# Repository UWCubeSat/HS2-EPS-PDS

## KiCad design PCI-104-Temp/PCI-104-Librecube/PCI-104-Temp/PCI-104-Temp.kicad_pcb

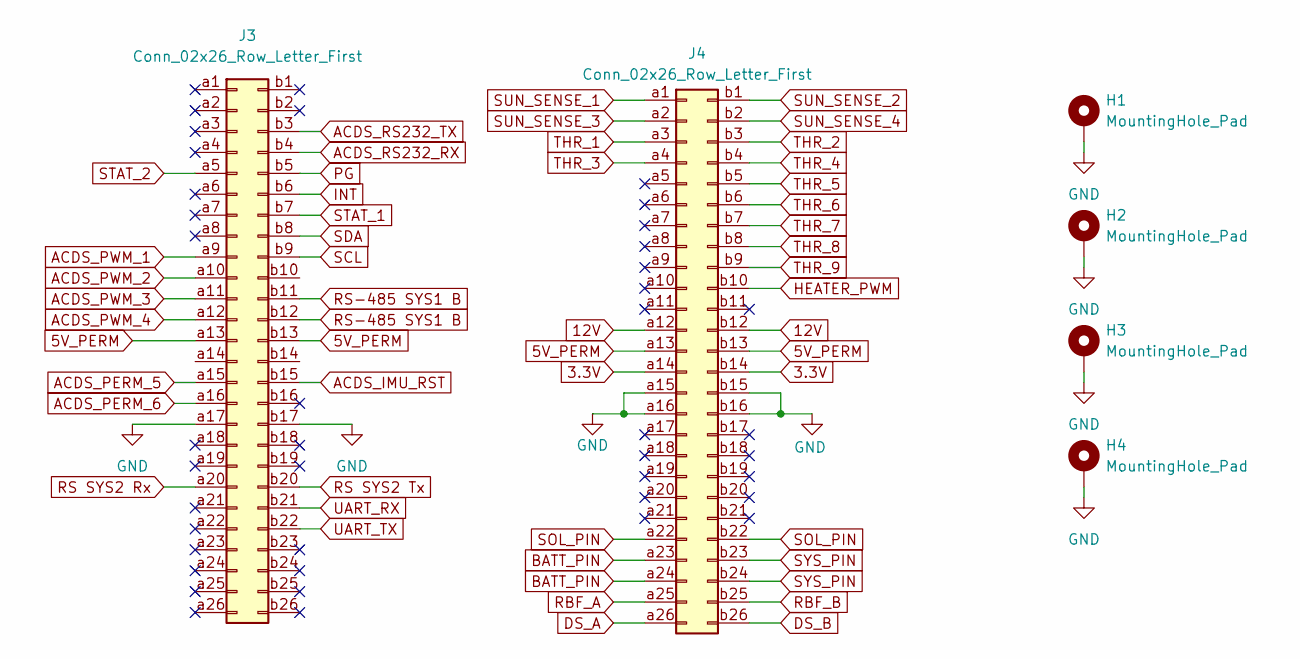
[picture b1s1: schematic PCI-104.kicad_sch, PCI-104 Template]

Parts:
H1, H2, H3, H4: MountingHole_Pad; MountingHole_3.2mm_M3_Pad
J3, J4: Conn_02x26_Row_Letter_First; PinSocket_2x26_P2.54mm_Vertical

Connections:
3.3V: J4.a14, J4.b14
5V_PERM: J3.a13, J3.b13, J4.a13, J4.b13
12V: J4.a12, J4.b12
ACDS_IMU_RST: J3.b15
ACDS_PERM_5: J3.a15
ACDS_PERM_6: J3.a16
ACDS_PWM_1: J3.a9
ACDS_PWM_2: J3.a10
ACDS_PWM_3: J3.a11
ACDS_PWM_4: J3.a12
ACDS_RS232_RX: J3.b4
ACDS_RS232_TX: J3.b3
BATT_PIN: J4.a23, J4.a24
DS_A: J4.a26
DS_B: J4.b26
GND: H1.1 (1_1), H2.1 (1_1), H3.1 (1_1), H4.1 (1_1), J3.a17, J3.b17, J4.a15, J4.a16, J4.b15, J4.b16
HEATER_PWM: J4.b10
INT: J3.b6
PG: J3.b5
RBF_A: J4.a25
RBF_B: J4.b25
RS SYS2 Rx: J3.a20
RS SYS2 Tx: J3.b20
RS-485 SYS1 B: J3.b11, J3.b12
SCL: J3.b9
SDA: J3.b8
SOL_PIN: J4.a22, J4.b22
STAT_1: J3.b7
STAT_2: J3.a5
SUN_SENSE_1: J4.a1
SUN_SENSE_2: J4.b1
SUN_SENSE_3: J4.a2
SUN_SENSE_4: J4.b2
SYS_PIN: J4.b23, J4.b24
THR_1: J4.a3
THR_2: J4.b3
THR_3: J4.a4
THR_4: J4.b4
THR_5: J4.b5
THR_6: J4.b6
THR_7: J4.b7
THR_8: J4.b8
THR_9: J4.b9
UART_RX: J3.b21
UART_TX: J3.b22

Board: 2 copper layers, 6 parts (0 on the bottom side), 8 nets, no tracks yet.

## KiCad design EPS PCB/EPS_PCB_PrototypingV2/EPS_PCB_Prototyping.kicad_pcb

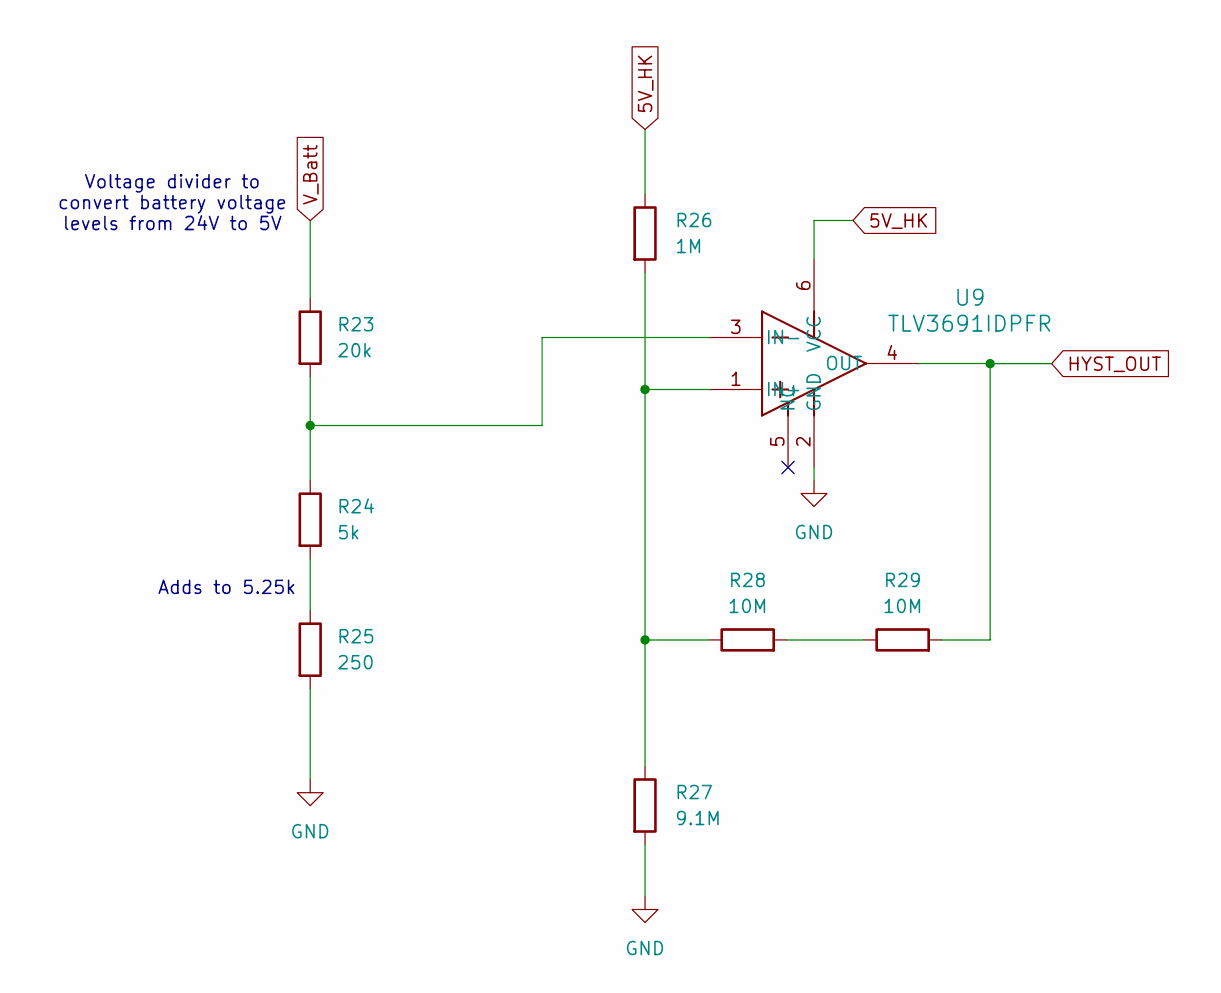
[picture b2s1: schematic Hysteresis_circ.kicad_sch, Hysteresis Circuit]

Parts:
R23: 20k; R_0603_1608Metric
R24: 5k; R_0603_1608Metric
R25: 250; R_0603_1608Metric
R26: 1M; R_1206_3216Metric
R27: 9.1M; R_1206_3216Metric
R28, R29: 10M; R_1206_3216Metric
U9: TLV3691IDPFR

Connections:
5V_HK: R26.1, U9.6 (VCC); also elsewhere on the board
GND: R25.2, R27.2, U9.2 (GND); also elsewhere on the board
HYST_OUT: R29.2, U9.4 (OUT)
unnamed: R24.2, R25.1
unnamed: R28.2, R29.1
unnamed: R26.2, R27.1, R28.1, U9.1 (IN+)
unnamed: R23.2, R24.1, U9.3 (IN-)

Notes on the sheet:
Adds to 5.25k
Voltage divider to convert battery voltage levels from 24V to 5V

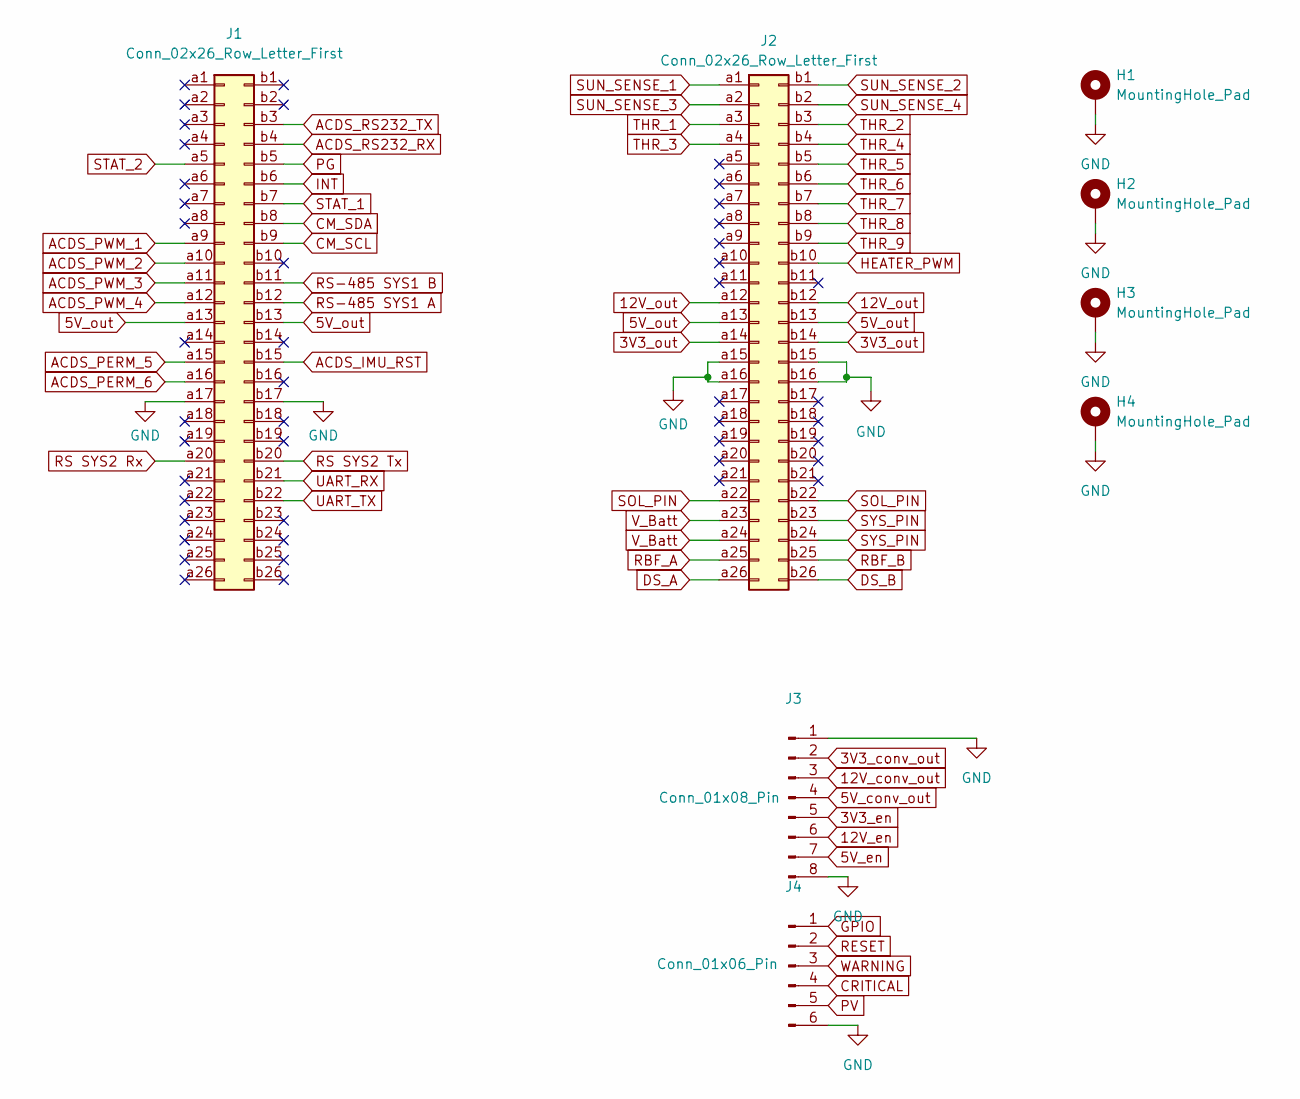
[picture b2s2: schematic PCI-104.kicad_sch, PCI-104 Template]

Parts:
H1, H2, H3, H4: MountingHole_Pad; MountingHole_3.2mm_M3_Pad
J1, J2: Conn_02x26_Row_Letter_First; PinSocket_2x26_P2.54mm_Vertical
J3: Conn_01x08_Pin; PinHeader_1x08_P2.54mm_Vertical
J4: Conn_01x06_Pin; PinHeader_1x06_P2.54mm_Horizontal

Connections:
3V3_conv_out: J3.2; also elsewhere on the board
3V3_en: J3.5; also elsewhere on the board
3V3_out: J2.a14, J2.b14; also elsewhere on the board
5V_conv_out: J3.4; also elsewhere on the board
5V_en: J3.7; also elsewhere on the board
5V_out: J1.a13, J1.b13, J2.a13, J2.b13; also elsewhere on the board
12V_conv_out: J3.3; also elsewhere on the board
12V_en: J3.6; also elsewhere on the board
12V_out: J2.a12, J2.b12; also elsewhere on the board
ACDS_IMU_RST: J1.b15
ACDS_PERM_5: J1.a15
ACDS_PERM_6: J1.a16
ACDS_PWM_1: J1.a9
ACDS_PWM_2: J1.a10
ACDS_PWM_3: J1.a11
ACDS_PWM_4: J1.a12
ACDS_RS232_RX: J1.b4
ACDS_RS232_TX: J1.b3
CM_SCL: J1.b9; also elsewhere on the board
CM_SDA: J1.b8; also elsewhere on the board
CRITICAL: J4.4; also elsewhere on the board
DS_A: J2.a26
DS_B: J2.b26
GND: H1.1 (1_1), H2.1 (1_1), H3.1 (1_1), H4.1 (1_1), J1.a17, J1.b17, J2.a15, J2.a16, J2.b15, J2.b16, J3.1, J3.8, J4.6; also elsewhere on the board
GPIO: J4.1; also elsewhere on the board
HEATER_PWM: J2.b10
INT: J1.b6
PG: J1.b5
PV: J4.5; also elsewhere on the board
RBF_A: J2.a25
RBF_B: J2.b25
RESET: J4.2; also elsewhere on the board
RS SYS2 Rx: J1.a20
RS SYS2 Tx: J1.b20
RS-485 SYS1 A: J1.b12
RS-485 SYS1 B: J1.b11
SOL_PIN: J2.a22, J2.b22
STAT_1: J1.b7
STAT_2: J1.a5
SUN_SENSE_1: J2.a1
SUN_SENSE_2: J2.b1
SUN_SENSE_3: J2.a2
SUN_SENSE_4: J2.b2
SYS_PIN: J2.b23, J2.b24
THR_1: J2.a3
THR_2: J2.b3
THR_3: J2.a4
THR_4: J2.b4
THR_5: J2.b5
THR_6: J2.b6
THR_7: J2.b7
THR_8: J2.b8
THR_9: J2.b9
UART_RX: J1.b21
UART_TX: J1.b22
WARNING: J4.3; also elsewhere on the board

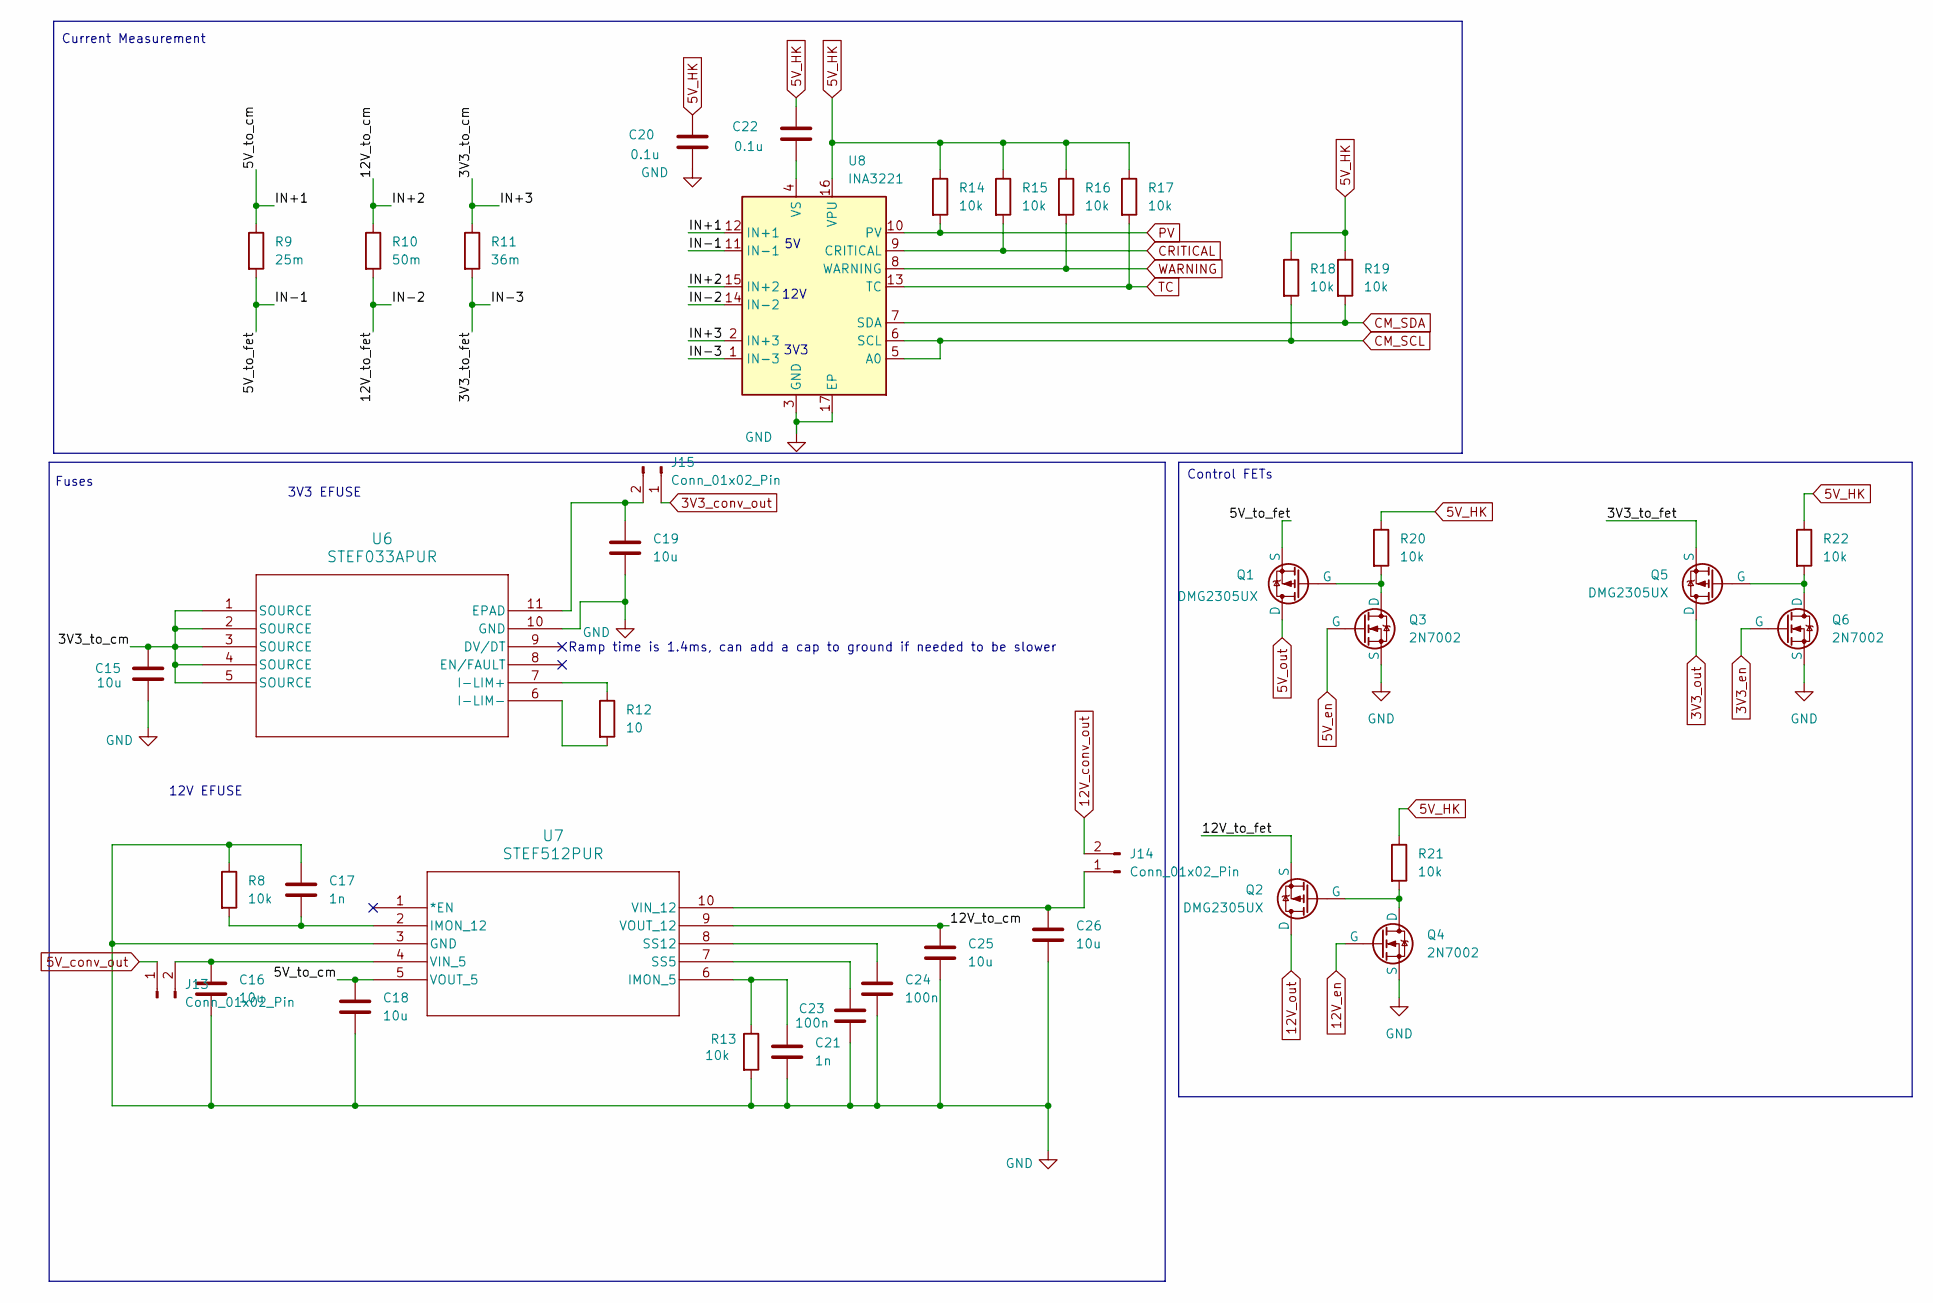
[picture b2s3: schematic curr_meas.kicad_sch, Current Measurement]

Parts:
C15, C16, C18, C19, C25, C26: 10u; C_0603_1608Metric
C17, C21: 1n; C_0603_1608Metric
C20, C22: 0.1u; C_0603_1608Metric
C23, C24: 100n; C_0603_1608Metric
J13, J14, J15: Conn_01x02_Pin; PinSocket_1x02_P2.54mm_Vertical
Q1, Q2, Q5: DMG2305UX; SOT-23-3
Q3, Q4, Q6: 2N7002; SOT-23-3
R8, R13, R14, R15, R16, R17, R18, R19: 10k; R_0603_1608Metric
R9: 25m; RES_VISHAY_WSLP2512_A_VIS
R10: 50m; RES_VISHAY_WSLP2512_A_VIS
R11: 36m; RES_VISHAY_WSLP2512_A_VIS
R12: 10; R_0603_1608Metric
R20, R21, R22: 10k; R_1206_3216Metric
U6: STEF033APUR; STEF033
U7: STEF512PUR; QFN10_2X3_STM-L
U8: INA3221; Texas_RGV0016A_VQFN-16-1EP_4x4mm_P0.65mm_EP2.1x2.1mm

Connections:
3V3_conv_out: J15.1; also elsewhere on the board
3V3_en: Q6.2 (G); also elsewhere on the board
3V3_out: Q5.1 (D); also elsewhere on the board
5V_HK: C20.1, C22.1, R14.1, R15.1, R16.1, R17.1, R18.1, R19.1, R20.1, R21.1, R22.1, U8.16 (VPU); also elsewhere on the board
5V_conv_out: J13.1; also elsewhere on the board
5V_en: Q3.2 (G); also elsewhere on the board
5V_out: Q1.1 (D); also elsewhere on the board
12V_conv_out: J14.2; also elsewhere on the board
12V_en: Q4.2 (G); also elsewhere on the board
12V_out: Q2.1 (D); also elsewhere on the board
/Curr_meas/3V3_to_cm: C15.1, R11.1, U6.1 (SOURCE), U6.2 (SOURCE), U6.3 (SOURCE), U6.4 (SOURCE), U6.5 (SOURCE), U8.2 (IN+3)
/Curr_meas/3V3_to_fet: Q5.3 (S), R11.2, U8.1 (IN-3)
/Curr_meas/5V_to_cm: C18.1, R9.1, U7.5 (VOUT_5), U8.12 (IN+1)
/Curr_meas/5V_to_fet: Q1.3 (S), R9.2, U8.11 (IN-1)
/Curr_meas/12V_to_cm: C25.1, R10.1, U7.9 (VOUT_12), U8.15 (IN+2)
/Curr_meas/12V_to_fet: Q2.3 (S), R10.2, U8.14 (IN-2)
CM_SCL: R18.2, U8.5 (A0), U8.6 (SCL); also elsewhere on the board
CM_SDA: R19.2, U8.7 (SDA); also elsewhere on the board
CRITICAL: R15.2, U8.9 (CRITICAL); also elsewhere on the board
GND: C15.2, C16.2, C17.1, C18.2, C19.2, C20.2, C21.2, C23.2, C24.2, C25.2, C26.2, Q3.3 (S), Q4.3 (S), Q6.3 (S), R8.1, R13.2, U6.10 (GND), U7.3 (GND), U8.3 (GND), U8.17 (EP); also elsewhere on the board
unnamed: C16.1, J13.2, U7.4 (VIN_5)
unnamed: C26.1, J14.1, U7.10 (VIN_12)
unnamed: C19.1, J15.2, U6.11 (EPAD)
unnamed: Q1.2 (G), Q3.1 (D), R20.2
unnamed: Q2.2 (G), Q4.1 (D), R21.2
unnamed: Q5.2 (G), Q6.1 (D), R22.2
unnamed: R12.1, U6.7 (I-LIM+)
unnamed: R12.2, U6.6 (I-LIM-)
unnamed: C21.1, R13.1, U7.6 (IMON_5)
unnamed: C17.2, R8.2, U7.2 (IMON_12)
unnamed: C23.1, U7.7 (SS5)
unnamed: C24.1, U7.8 (SS12)
unnamed: C22.2, U8.4 (VS)
PV: R14.2, U8.10 (PV); also elsewhere on the board
TC: R17.2, U8.13 (TC)
WARNING: R16.2, U8.8 (WARNING); also elsewhere on the board

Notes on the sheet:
12V
Current Measurement
3V3 EFUSE
3V3
Ramp time is 1.4ms, can add a cap to ground if needed to be slower
12V EFUSE
Control FETs
Fuses

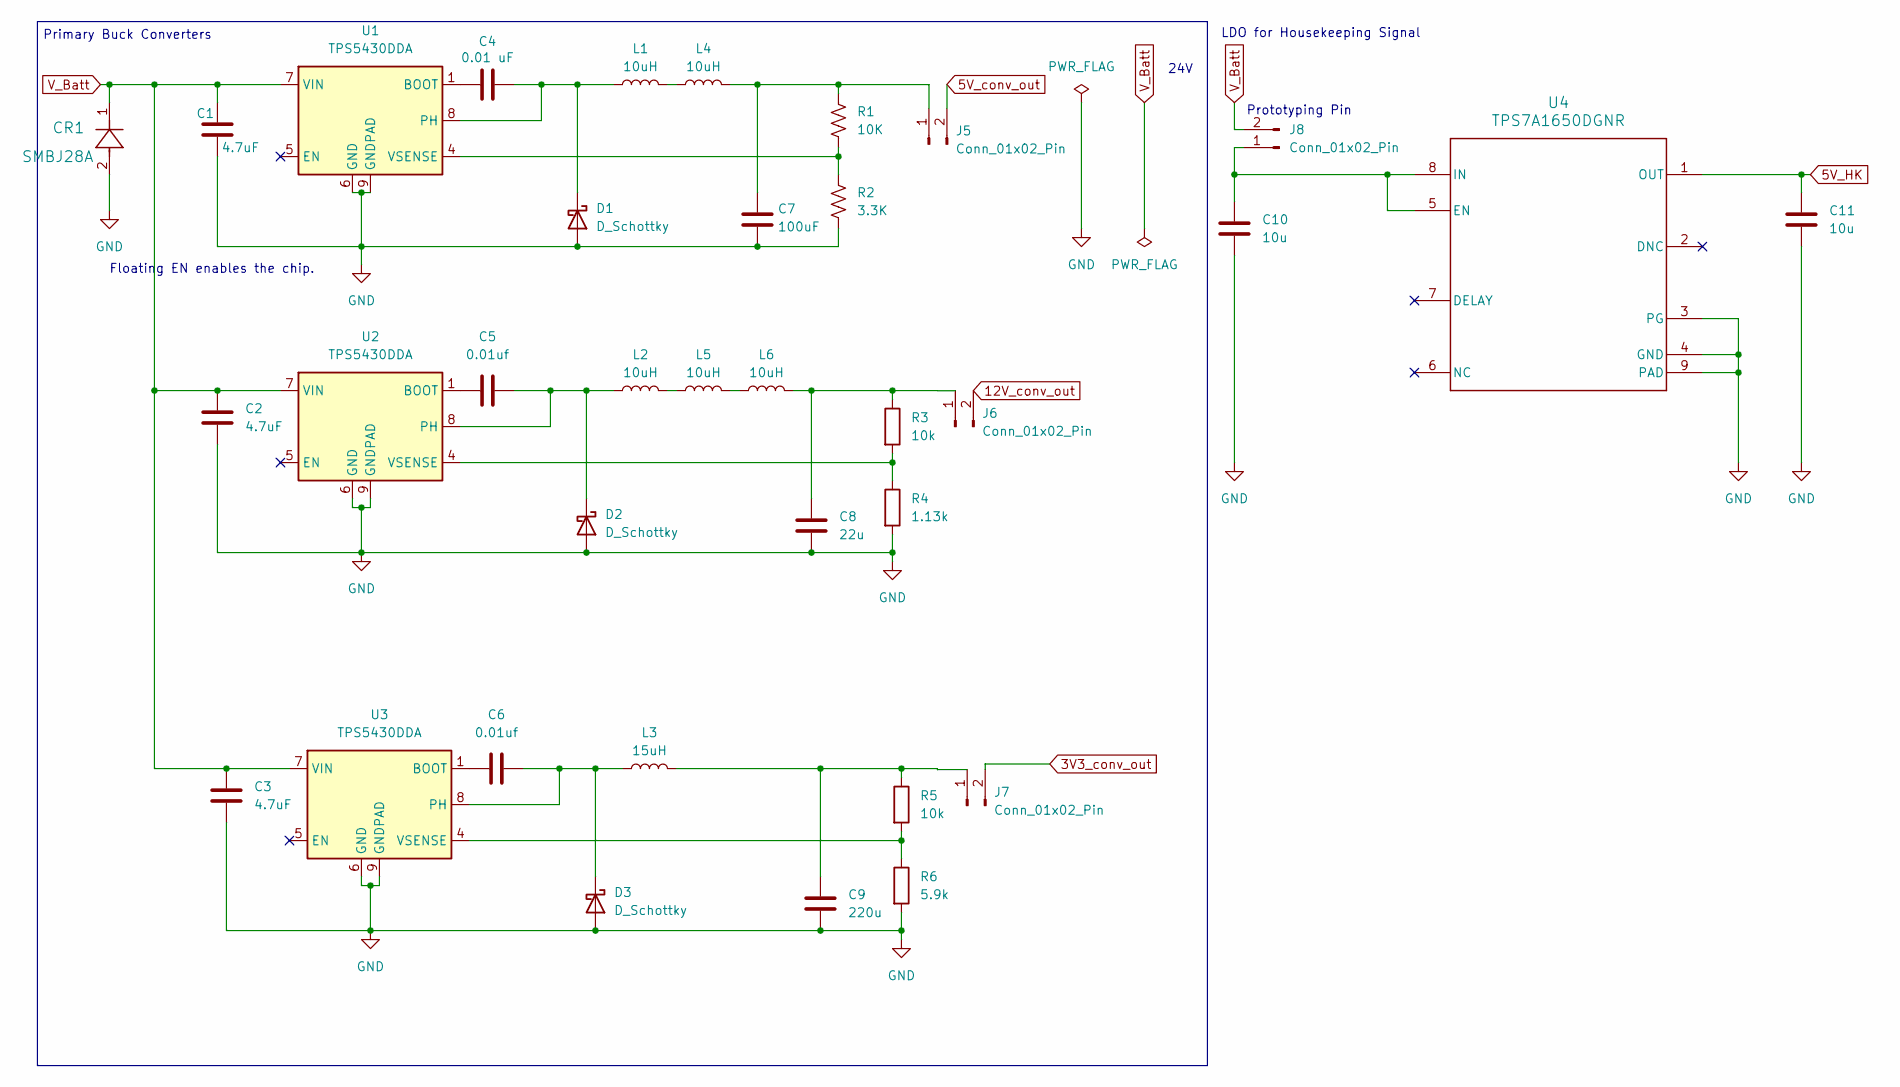
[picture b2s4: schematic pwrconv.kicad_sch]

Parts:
C1, C2, C3: 4.7uF; C_0805_2012Metric; LCSC C1779
C4: 0.01 uF; C_0603_1608Metric; LCSC C1589
C5, C6: 0.01uf; C_0603_1608Metric; LCSC C1589
C7: 100uF; C_0805_2012Metric; LCSC C2836437
C8: 22u; C_0805_2012Metric; LCSC C45783
C9: 220u; C_0805_2012Metric; LCSC C125977
C10, C11: 10u; C_0603_1608Metric
CR1: SMBJ28A; DIODE_DO214AA
D1, D2, D3: D_Schottky; D_SOD-323; LCSC C191023
J5, J6, J7, J8: Conn_01x02_Pin; PinSocket_1x02_P2.54mm_Vertical
L1, L2, L4, L5, L6: 10uH; L_Changjiang_FXL0630; LCSC C167223
L3: 15uH; L_Changjiang_FXL0630; LCSC C40000
R1: 10K; R_0603_1608Metric; LCSC C15401
R2: 3.3K; R_1206_3216Metric; LCSC C26041
R3, R5: 10k; R_0603_1608Metric; LCSC C15401
R4: 1.13k; R_1206_3216Metric; LCSC C4410
R6: 5.9k; R_1206_3216Metric; LCSC C488883
U1, U2, U3: TPS5430DDA; TI_SO-PowerPAD-8_ThermalVias; LCSC C9864
U4: TPS7A1650DGNR; DGN0008C_N

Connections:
3V3_conv_out: J7.2; also elsewhere on the board
5V_HK: C11.2, U4.1 (OUT); also elsewhere on the board
5V_conv_out: J5.2; also elsewhere on the board
12V_conv_out: J6.2; also elsewhere on the board
GND: C1.2, C2.2, C3.2, C7.2, C8.1, C9.1, C10.1, C11.1, CR1.2, D1.2 (A), D2.2 (A), D3.2 (A), R2.2, R4.2, R6.2, U1.6 (GND), U1.9 (GNDPAD), U2.6 (GND), U2.9 (GNDPAD), U3.6 (GND), U3.9 (GNDPAD), U4.3 (PG), U4.4 (GND), U4.9 (PAD); also elsewhere on the board
unnamed: C4.2, D1.1 (K), L1.1, U1.8 (PH)
unnamed: C5.2, D2.1 (K), L2.1, U2.8 (PH)
unnamed: C6.2, D3.1 (K), L3.1, U3.8 (PH)
unnamed: C7.1, J5.1, L4.2, R1.1
unnamed: C8.2, J6.1, L6.2, R3.1
unnamed: C9.2, J7.1, L3.2, R5.1
unnamed: C10.2, J8.1, U4.5 (EN), U4.8 (IN)
unnamed: L1.2, L4.1
unnamed: L2.2, L5.1
unnamed: L5.2, L6.1
unnamed: C4.1, U1.1 (BOOT)
unnamed: R1.2, R2.1, U1.4 (VSENSE)
unnamed: C5.1, U2.1 (BOOT)
unnamed: R3.2, R4.1, U2.4 (VSENSE)
unnamed: C6.1, U3.1 (BOOT)
unnamed: R5.2, R6.1, U3.4 (VSENSE)

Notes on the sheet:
Primary Buck Converters
LDO for Housekeeping Signal
Prototyping Pin
24V
Floating EN enables the chip.

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
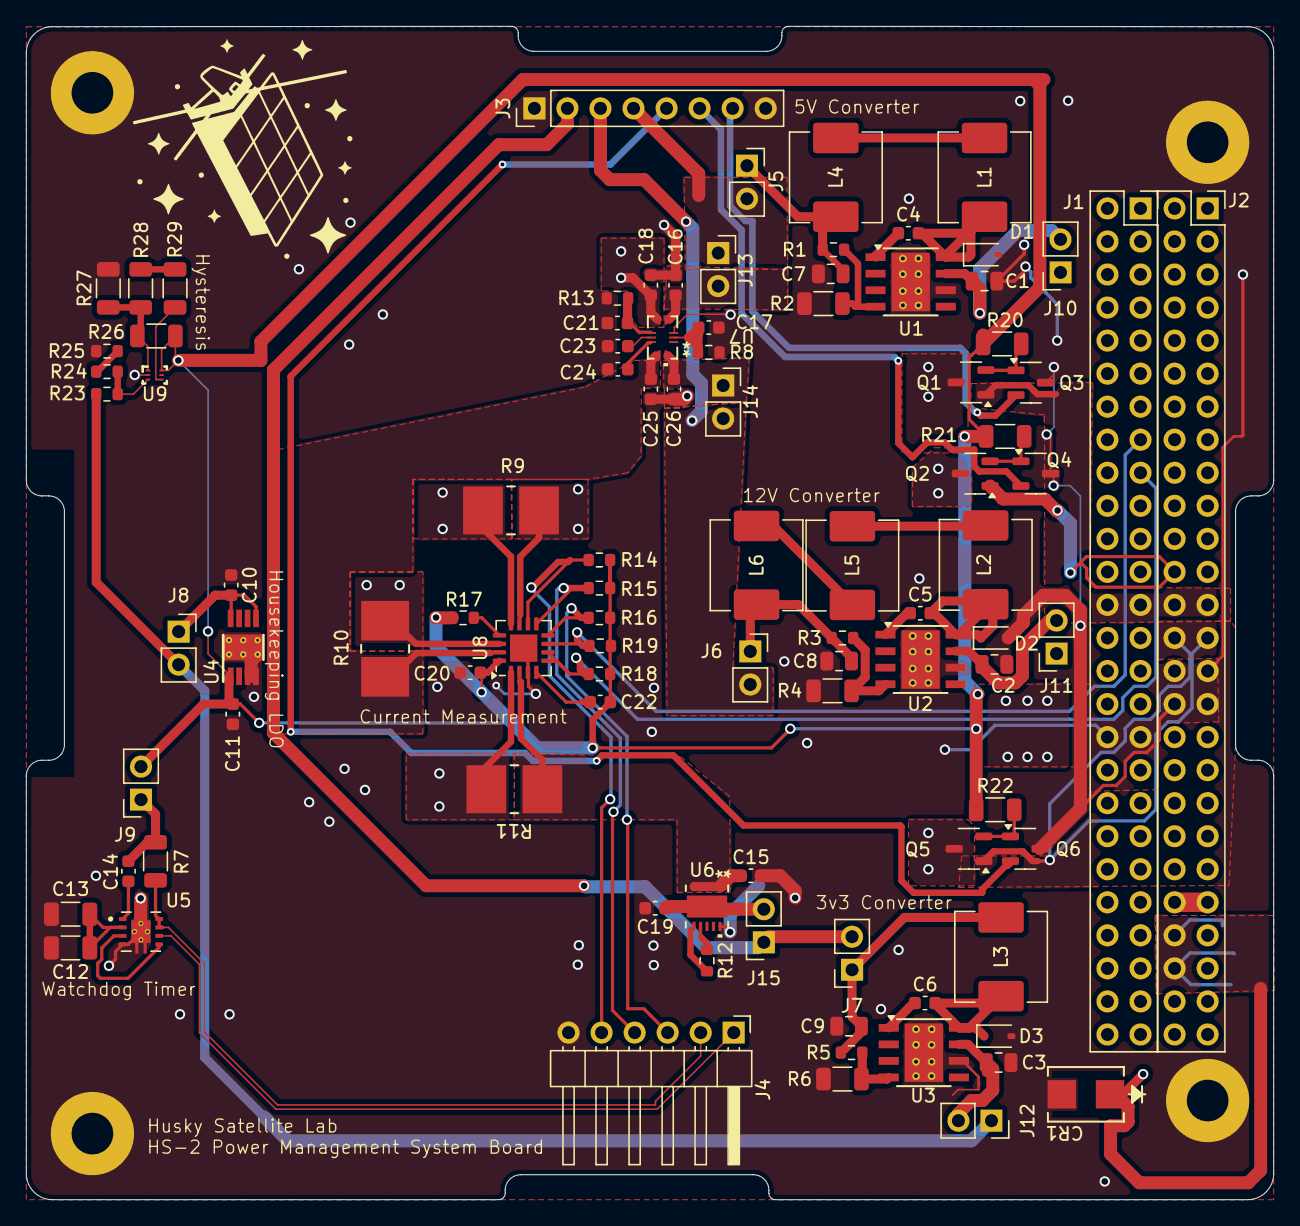
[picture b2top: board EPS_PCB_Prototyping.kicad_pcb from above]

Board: 2 copper layers, 95.9 x 90.2 mm, 99 parts (0 on the bottom side), 69 nets.

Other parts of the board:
C12: 680nF; C_1206_3216Metric
C13: 82nF; C_1206_3216Metric
C14: 0.1uF; C_0603_1608Metric
J9, J10, J11, J12: Conn_01x02_Pin; PinSocket_1x02_P2.54mm_Vertical
R7: 100k; R_1206_3216Metric
U5: TPS3431SDRBR; IC_TPS3431SDRBR

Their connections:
5V_HK: J9.2; also elsewhere on the board
/watchdog_timer/conn: C14.1, J9.1, R7.1
GND: C12.2, C13.2, U5.4 (GND), U5.9 (EXP); also elsewhere on the board
GPIO: U5.6 (WDI); also elsewhere on the board
unnamed: C12.1, C13.1, U5.2 (CWD)
unnamed: U5.3 (EN), U5.5 (SET1)
unnamed: C14.2, U5.1 (VDD)
RESET: R7.2, U5.7 (~WDO), U5.8 (ENOUT); also elsewhere on the board

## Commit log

2026-04-27 HS2 Repository Clone
    Pushed EPS PDS repo to new place
2026-05-17 EPS PCB Ready for Order
2026-05-20 Small PC104 Template Fix
2026-05-22 PDS Ordered
2026-05-29 updated PC104 ADCS pins
